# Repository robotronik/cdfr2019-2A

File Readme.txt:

This is the Readme of this repository.

Robotronik Phelma 2018-2019

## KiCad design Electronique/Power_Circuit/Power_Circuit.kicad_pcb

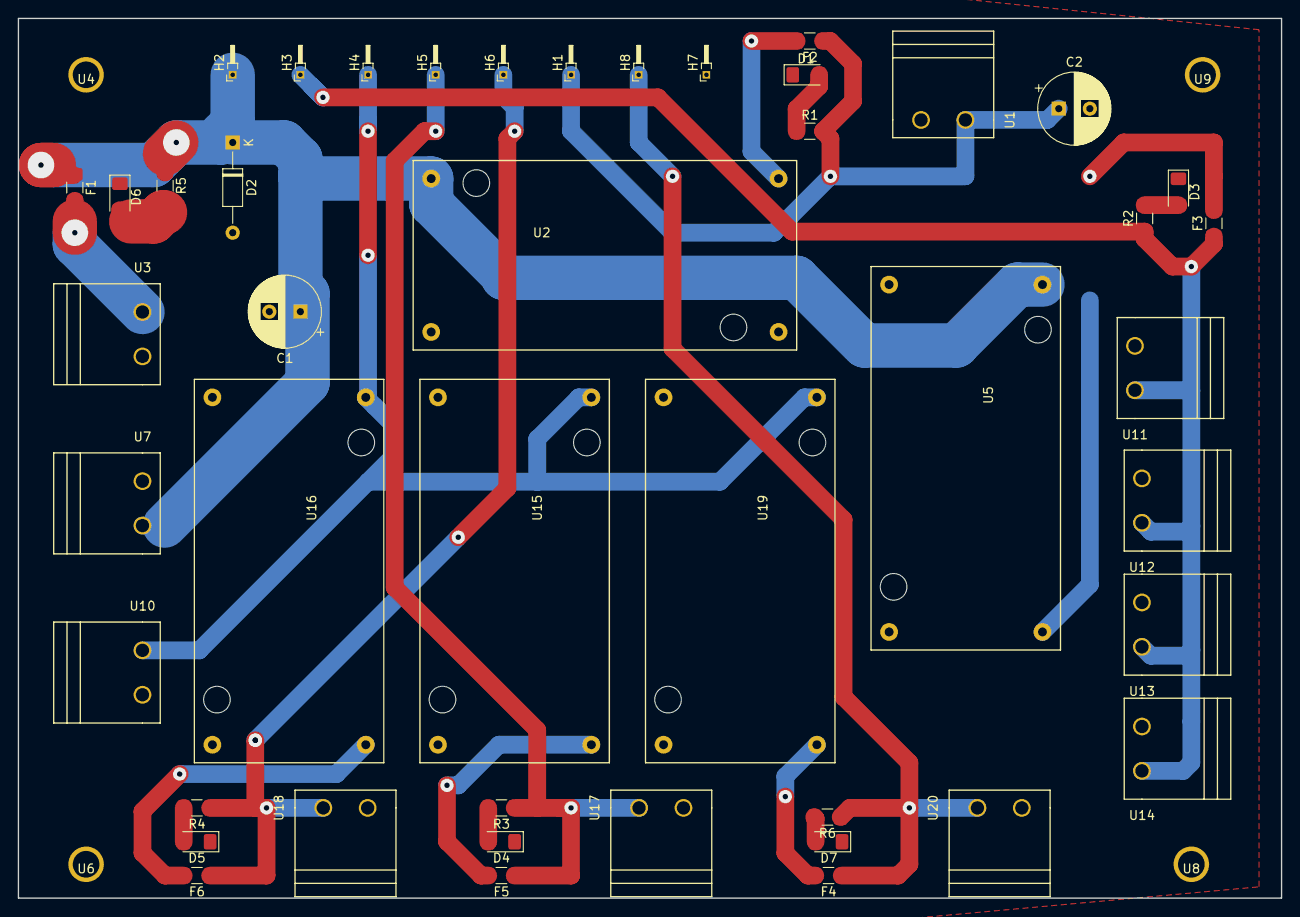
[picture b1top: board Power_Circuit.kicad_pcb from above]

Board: 2 copper layers, 142.2 x 99.1 mm, 49 parts (0 on the bottom side), 20 nets.

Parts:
C1, C2: CP; CP_Radial_D8.0mm_P3.50mm
D1, D3, D4, D5, D6, D7: LED; LED_1206_3216Metric_Pad1.42x1.75mm_HandSolder
D2: D; D_DO-35_SOD27_P10.16mm_Horizontal
F1, F2, F3, F4, F5, F6: Fuse; Fuse_1206_3216Metric_Pad1.42x1.75mm_HandSolder
H1, H2, H3, H4, H5, H6, H7, H8: MountingHole_Pad; PinHeader_1x01_P1.00mm_Horizontal
R1, R2, R3, R4, R5, R6: R; R_1206_3216Metric_Pad1.42x1.75mm_HandSolder
U1, U3, U7, U10, U11, U12, U13, U14, U17, U18, U20: B_Plug_5mm; B plug 5mm
U2, U5, U15, U16, U19: DSN2596
U4, U6, U8, U9: trou-d3mm; trou_d3mm

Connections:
12V: H4.1, U10.1, U15.1, U16.1, U19.1
18V: C1.1, D2.1, F1.1, H2.1, R5.1, U2.1, U5.1, U7.2
GND: C1.2, C2.2, D1.1, D2.2, D3.1, D4.1, D5.1, D6.1, D7.1, H7.1, U1.2, U2.2, U2.3, U3.2, U4.1, U5.2, U5.3, U6.1, U7.1, U8.1, U9.1, U10.2, U11.2, U12.2, U13.2, U14.2, U15.2, U15.3, U16.2, U16.3, U17.2, U18.2, U19.2, U19.3, U20.2
Logical_10V: F3.1, H3.1, R2.1, U11.1, U12.1, U13.1, U14.1
Motor1_12V: F5.1, H5.1, R3.1, U17.1
Motor2_12V: F6.1, H6.1, R4.1, U18.1
MotorExt_12V: F4.1, H8.1, R6.1, U20.1
unnamed: D1.2, R1.1
unnamed: D3.2, R2.2
unnamed: D4.2, R3.2
unnamed: D5.2, R4.2
unnamed: D6.2, R5.2
unnamed: D7.2, R6.2
unnamed: F1.2, U3.1
unnamed: F2.2, U2.4
unnamed: F3.2, U5.4
unnamed: F4.2, U19.4
unnamed: F5.2, U15.4
unnamed: F6.2, U16.4
Raspberr_5V: C2.1, F2.1, H1.1, R1.2, U1.1

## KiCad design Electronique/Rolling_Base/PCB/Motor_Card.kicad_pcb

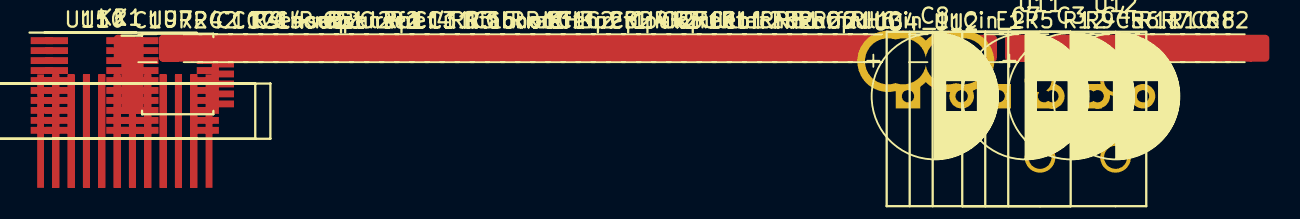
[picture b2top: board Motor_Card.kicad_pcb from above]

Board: 2 copper layers, 77 parts (0 on the bottom side), 43 nets, no tracks yet.

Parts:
C1, C2, C5, C6, C13, C14, C15: 100n; C_1206_3216Metric_Pad1.42x1.75mm_HandSolder
C3, C4: 100u; CP_Radial_D8.0mm_P3.50mm
C7, C8: 10u; CP_Radial_D8.0mm_P3.50mm
C9, C10, C11, C12: 0,1u; C_1206_3216Metric_Pad1.42x1.75mm_HandSolder
Cboot1, Cboot2: 220n; C_1206_3216Metric_Pad1.42x1.75mm_HandSolder
Cen1, Cen2: 5.6n; C_1206_3216Metric_Pad1.42x1.75mm_HandSolder
Cin_1, Cin_2: 0,1u; C_1206_3216Metric_Pad1.42x1.75mm_HandSolder
Coff1, Coff2: 1n; C_1206_3216Metric_Pad1.42x1.75mm_HandSolder
Cp1, Cp2: 10n; C_1206_3216Metric_Pad1.42x1.75mm_HandSolder
Cpul1, Cpul2: 10n; C_1206_3216Metric_Pad1.42x1.75mm_HandSolder
Cref1, Cref2: 10n; C_1206_3216Metric_Pad1.42x1.75mm_HandSolder
F1, F2: Fuse; Fuse_1206_3216Metric_Pad1.42x1.75mm_HandSolder
K1, K2: Maxon-200142; Molex-52610-1133
R1, R2, R3: 10k; R_1206_3216Metric_Pad1.42x1.75mm_HandSolder
R4, R9, R12: 470; R_1206_3216Metric_Pad1.42x1.75mm_HandSolder
R5, R6: 2k; R_1206_3216Metric_Pad1.42x1.75mm_HandSolder
R7: 820; R_1206_3216Metric_Pad1.42x1.75mm_HandSolder
R8: 270; R_1206_3216Metric_Pad1.42x1.75mm_HandSolder
R10: 370; R_1206_3216Metric_Pad1.42x1.75mm_HandSolder
R11: 220; R_1206_3216Metric_Pad1.42x1.75mm_HandSolder
RH1, RH2, RH3, RH4, RH5, RH6: 10k; R_1206_3216Metric_Pad1.42x1.75mm_HandSolder
Ren1, Ren2: 100k; R_1206_3216Metric_Pad1.42x1.75mm_HandSolder
Roff1, Roff2: 33k; R_1206_3216Metric_Pad1.42x1.75mm_HandSolder
Rp1, Rp2: 100; R_1206_3216Metric_Pad1.42x1.75mm_HandSolder
Rpul1, Rpul2: 47k; R_1206_3216Metric_Pad1.42x1.75mm_HandSolder
Rref1, Rref3: 1.2k; R_1206_3216Metric_Pad1.42x1.75mm_HandSolder
Rref2, Rref4: 220; R_1206_3216Metric_Pad1.42x1.75mm_HandSolder
Rsense1, Rsense2: 0.3; R_1206_3216Metric_Pad1.42x1.75mm_HandSolder
Rtacho1, Rtacho2: 1k; R_1206_3216Metric_Pad1.42x1.75mm_HandSolder
U1, U2, U3, U4: Trou-3
U7: 74HC00; TSSOP-14_4.4x5mm_P0.65mm
U9, U10, U15: txb0108; TSSOP-20_4.4x6.5mm_P0.65mm
U11, U12: B_Plug_5mm; B plug 5mm

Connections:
+3V3: C1.2, C8.1, C9.1, C11.1, C13.1, C14.1, C15.2, R11.1, R12.2, U7.14, U9.2, U9.10, U10.2, U10.10, U15.2, U15.10
+5V: C7.1, C10.1, C12.1, K1.11, K2.11, R8.1, R9.2, RH1.1, RH2.1, RH3.1, RH4.1, RH5.1, RH6.1, Rref1.1, Rref3.1, Rtacho1.1, Rtacho2.1, U9.19, U10.19, U15.19
+10V: C3.1, C5.1, Cin_1.1, Cin_2.1, F2.1, R6.2
+12V: C4.1, C6.1, Cboot1.1, Cboot2.1, F1.1, R5.2
/motor_part/DIAG_1: Cen1.2, Ren1.2, U9.15
/motor_part/DIAG_2: Cen2.2, Ren2.2, U10.20
/motor_part/EN_1: Ren1.1, U9.20
/motor_part/EN_2: Ren2.1, U9.18
/motor_part/Hall_sensor_11: K1.9, RH3.2
/motor_part/Hall_sensor_12: K2.9, RH6.2
/motor_part/Hall_sensor_21: K1.8, RH2.2
/motor_part/Hall_sensor_22: K2.8, RH5.2
/motor_part/Hall_sensor_31: K1.10, RH1.2
/motor_part/Hall_sensor_32: K2.10, RH4.2
/motor_part/Out_11: K1.1, K1.2
/motor_part/Out_12: K2.1, K2.2
/motor_part/Out_21: K1.3, K1.4
/motor_part/Out_22: K2.3, K2.4
/motor_part/Out_31: K1.5, K1.6
/motor_part/Out_33: K2.5, K2.6
/motor_part/TACHO_1: Rtacho1.2, U9.14
/motor_part/TACHO_2: Rtacho2.2, U10.18
/power_part/Alim_num: F2.2, U11.1
/power_part/Alim_puiss: F1.2, U12.1
/uC/Cmd_En_1(3V3): R1.1, U7.2
/uC/Cmd_En_2(3V3): R2.1, U7.10
/uC/nrst(3V3): C2.1, U7.1, U7.9
GND: C1.1, C2.2, C3.2, C5.2, C7.2, C8.2, C9.2, C10.2, C11.2, C12.2, C13.2, C14.2, C15.1, Cen1.1, Cen2.1, Cin_1.2, Cin_2.2, Coff1.1, Coff2.1, Cpul1.1, Cpul2.1, Cref1.2, Cref2.2, K1.7, K2.7, R1.2, R2.2, R7.2, R10.1, Roff1.1, Roff2.1, Rpul1.1, Rpul2.1, Rref2.2, Rref4.2, U1.1, U2.1, U3.1, U4.1, U7.7, U9.11, U10.11, U11.2, U15.11
GNDPWR: C4.2, C6.2, Rsense1.2, Rsense2.2, U12.2
unnamed: Coff1.2, Roff1.2
unnamed: Coff2.2, Roff2.2
unnamed: Cp1.1, Rp1.2
unnamed: Cp2.1, Rp2.2
unnamed: Cpul1.2, Rpul1.2
unnamed: Cpul2.2, Rpul2.2
unnamed: Cref1.1, Rref1.2, Rref2.1
unnamed: Cref2.1, Rref3.2, Rref4.1
unnamed: R7.1, R8.2
unnamed: R10.2, R11.2
unnamed: U7.3, U7.4, U7.5
unnamed: U7.6, U9.1
unnamed: U7.11, U9.3
unnamed: U7.8, U7.12, U7.13

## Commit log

2018-08-09 Update Readme.txt
    Just a test
2018-08-09 Update Readme.txt
    Test 2
2018-08-09 Test2
2018-08-09 Update Readme.txt
    test3
2018-08-09 Test 4
2018-08-09 Update Readme.txt
    test5
2018-08-09 Clean up
    clean up
2018-08-09 Test
2018-08-10 Add the gitignore -ignore *o files
2018-09-04 Add readme's informations
2018-11-16 Setup for the PID
2018-11-16 PID macros
2018-11-22 premier increment sur le devpment du pid, il reste le code du main , le code du pid a verifier
2018-11-29 Fixed pid and add pid control in the main
2018-12-06 Fix PID errors
2019-01-10 [ Electronik ] Realization of the electric schemes - Modification of the old rolling base card - Add of motor stop during reset - Conversion of tension (3V3) to the stm Commit before route
2019-01-30 Add lib
2019-02-01 cleanup of Kicad files, add gitignore
2019-02-01 Utilisation de chemin relatif au projet pour les librairies
2019-02-08 Final Rolling Base Card
2019-02-08 Circuit adjustement
2019-02-21 quick fix
